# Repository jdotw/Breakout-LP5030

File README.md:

# MP2359, LP5030 and TCA9544A Breakout Board

This breakout board allows you to test an LP5030 LED driver, with a TCA9544A i2c mux/hub, being powered by a MP2359 buck power converter. The board was design to be powered by +12V, but should work with anything from +5 to +12. Place a jumper across the 3.3V 2-pin header to enable the use of the onboard power supply. Or, supply 3.3V directly to the pin marked 3.3V to bypass the onboard power supply. 

I built this board because of a larger project where I wanted to use these three components. However, having not used them before in a design and without access to well priced evaluation board, I decided to make my own. TI sells an eval board for the LP5030 but it's $100+ which is ridiculous. There is a well priced board available to eval the MP2359 but it's rather huge. And so, I decided to build my own. 

The gerber and assembly files included herein have been successfully used with JLCPCB and their SMT Assembly surface to order these boards with everything but the LP5030, TCA9544A and headers already assembled. Those, you'll need to take care of yourself. 

If you have any questions you can find me on Twitter @scotchandcode, and streaming regularly at twitch.tv/jdotw. 

Datasheet links:

MP2359: https://www.monolithicpower.com/en/mp2359.html

LP5030: https://www.ti.com/product/LP5030

TCA9544A: https://www.ti.com/product/TCA9544A

Enjoy! 

-jw

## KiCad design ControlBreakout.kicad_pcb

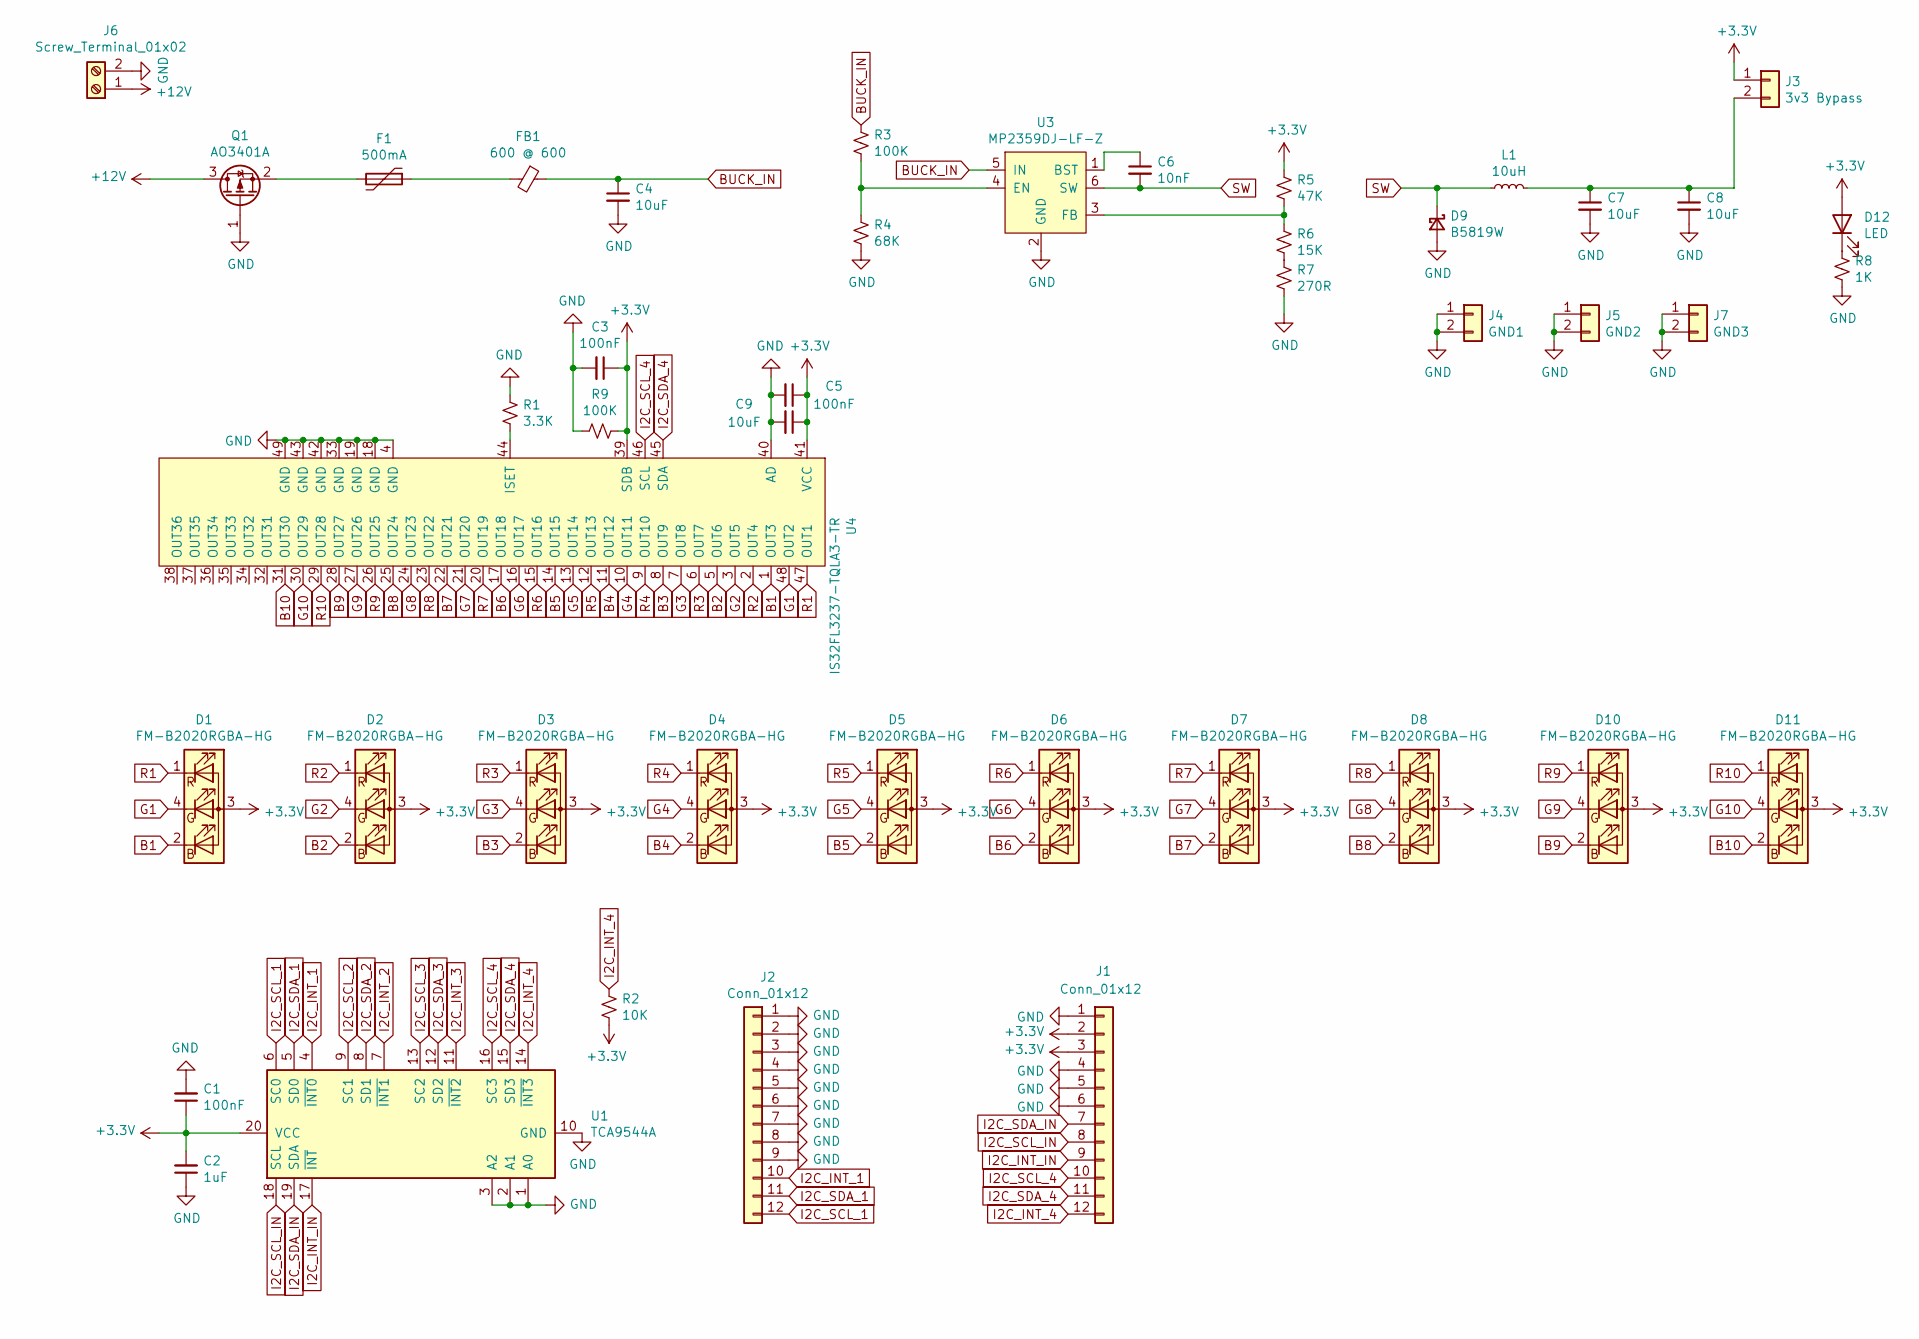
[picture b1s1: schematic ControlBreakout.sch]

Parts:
C1: 100nF; C_0402_1005Metric; LCSC C1525
C2: 1uF; C_0402_1005Metric; LCSC C52923
C3, C5: 100nF; C_0603_1608Metric; LCSC C14663
C4: 10uF; C_1206_3216Metric; LCSC C13585
C6: 10nF; C_0805_2012Metric; LCSC C1710
C7, C8: 10uF; C_1206_3216Metric; LCSC C19702
C9: 10uF; C_0603_1608Metric; LCSC C19702
D1, D2, D4, D5, D6, D7, D8, D10, D11: FM-B2020RGBA-HG; LCSC C108793
D3: FM-B2020RGBA-HG
D9: B5819W; D_SOD-123; LCSC C8598
D12: LED; LED_0603_1608Metric; LCSC C72041
F1: 500mA; Fuse_1206_3216Metric; LCSC C369159
FB1: 600 @ 600; L_0805_2012Metric; LCSC C1017
J1, J2: Conn_01x12; PinHeader_1x12_P2.54mm_Vertical
J3: 3v3 Bypass; PinHeader_1x02_P2.54mm_Vertical
J4: GND1; PinHeader_1x02_P2.54mm_Vertical
J5: GND2; PinHeader_1x02_P2.54mm_Vertical
J6: Screw_Terminal_01x02; TerminalBlock_bornier-2_P5.08mm
J7: GND3; PinHeader_1x02_P2.54mm_Vertical
L1: 10uH; L_Sunlord_MWSA0518_5.4x5.2mm; LCSC C139506
Q1: AO3401A; SOT-23; LCSC C15127
R1: 3.3K; R_0603_1608Metric; LCSC C22978
R2: 10K; R_0603_1608Metric; LCSC C25804
R3: 100K; R_1206_3216Metric; LCSC C17900
R4: 68K; R_0603_1608Metric; LCSC C23231
R5: 47K; R_0603_1608Metric; LCSC C25819
R6: 15K; R_0603_1608Metric; LCSC C22809
R7: 270R; R_0603_1608Metric; LCSC C22966
R8: 1K; R_0603_1608Metric; LCSC C21190
R9: 100K; R_0603_1608Metric; LCSC C25803
U1: TCA9544A; TSSOP-20_4.4x6.5mm_P0.65mm
U3: MP2359DJ-LF-Z; TSOT-23-6; LCSC C14259
U4: IS32FL3237-TQLA3-TR; TQFP-48-1EP_7x7mm_P0.5mm_EP5x5mm

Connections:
+3V3: C1.1, C2.2, C3.1, C5.1, C9.1, D1.3 (+), D2.3 (+), D3.3 (+), D4.3 (+), D5.3 (+), D6.3 (+), D7.3 (+), D8.3 (+), D10.3 (+), D11.3 (+), D12.2 (A), J1.2, J1.3, J3.1, R2.2, R5.1, R9.2, U1.20 (VCC), U4.39 (SDB), U4.41 (VCC)
+12V: J6.1, Q1.3 (D)
B1: D1.2 (B-), U4.1 (OUT3)
B2: D2.2 (B-), U4.5 (OUT6)
B3: D3.2 (B-), U4.8 (OUT9)
B4: D4.2 (B-), U4.11 (OUT12)
B5: D5.2 (B-), U4.14 (OUT15)
B6: D6.2 (B-), U4.17 (OUT18)
B7: D7.2 (B-), U4.22 (OUT21)
B8: D8.2 (B-), U4.25 (OUT24)
B9: D10.2 (B-), U4.28 (OUT27)
B10: D11.2 (B-), U4.31 (OUT30)
BUCK_IN: C4.1, FB1.1, R3.1, U3.5 (IN)
G1: D1.4 (G-), U4.48 (OUT2)
G2: D2.4 (G-), U4.3 (OUT5)
G3: D3.4 (G-), U4.7 (OUT8)
G4: D4.4 (G-), U4.10 (OUT11)
G5: D5.4 (G-), U4.13 (OUT14)
G6: D6.4 (G-), U4.16 (OUT17)
G7: D7.4 (G-), U4.21 (OUT20)
G8: D8.4 (G-), U4.24 (OUT23)
G9: D10.4 (G-), U4.27 (OUT26)
G10: D11.4 (G-), U4.30 (OUT29)
GND: C1.2, C2.1, C3.2, C4.2, C5.2, C7.2, C8.2, C9.2, D9.2 (A), J1.1, J1.4, J1.5, J1.6, J2.1, J2.2, J2.3, J2.4, J2.5, J2.6, J2.7, J2.8, J2.9, J4.1, J4.2, J5.1, J5.2, J6.2, J7.1, J7.2, Q1.1 (G), R1.1, R4.2, R7.2, R8.2, R9.1, U1.1 (A0), U1.2 (A1), U1.3 (A2), U1.10 (GND), U3.2 (GND), U4.4 (GND), U4.18 (GND), U4.19 (GND), U4.33 (GND), U4.40 (AD), U4.42 (GND), U4.43 (GND), U4.49 (GND)
I2C_INT_1: J2.10, U1.4 (~INT0)
I2C_INT_2: U1.7 (~INT1)
I2C_INT_3: U1.11 (~INT2)
I2C_INT_4: J1.12, R2.1, U1.14 (~INT3)
I2C_INT_IN: J1.9, U1.17 (~INT)
I2C_SCL_1: J2.12, U1.6 (SC0)
I2C_SCL_2: U1.9 (SC1)
I2C_SCL_3: U1.13 (SC2)
I2C_SCL_4: J1.10, U1.16 (SC3), U4.46 (SCL)
I2C_SCL_IN: J1.8, U1.18 (SCL)
I2C_SDA_1: J2.11, U1.5 (SD0)
I2C_SDA_2: U1.8 (SD1)
I2C_SDA_3: U1.12 (SD2)
I2C_SDA_4: J1.11, U1.15 (SD3), U4.45 (SDA)
I2C_SDA_IN: J1.7, U1.19 (SDA)
unnamed: C6.1, U3.1 (BST)
unnamed: C7.1, C8.1, J3.2, L1.2
unnamed: D12.1 (K), R8.1
unnamed: F1.1, FB1.2
unnamed: F1.2, Q1.2 (S)
unnamed: R1.2, U4.44 (ISET)
unnamed: R3.2, R4.1, U3.4 (EN)
unnamed: R5.2, R6.1, U3.3 (FB)
unnamed: R6.2, R7.1
R1: D1.1 (R-), U4.47 (OUT1)
R2: D2.1 (R-), U4.2 (OUT4)
R3: D3.1 (R-), U4.6 (OUT7)
R4: D4.1 (R-), U4.9 (OUT10)
R5: D5.1 (R-), U4.12 (OUT13)
R6: D6.1 (R-), U4.15 (OUT16)
R7: D7.1 (R-), U4.20 (OUT19)
R8: D8.1 (R-), U4.23 (OUT22)
R9: D10.1 (R-), U4.26 (OUT25)
R10: D11.1 (R-), U4.29 (OUT28)
SW: C6.2, D9.1 (K), L1.1, U3.6 (SW)

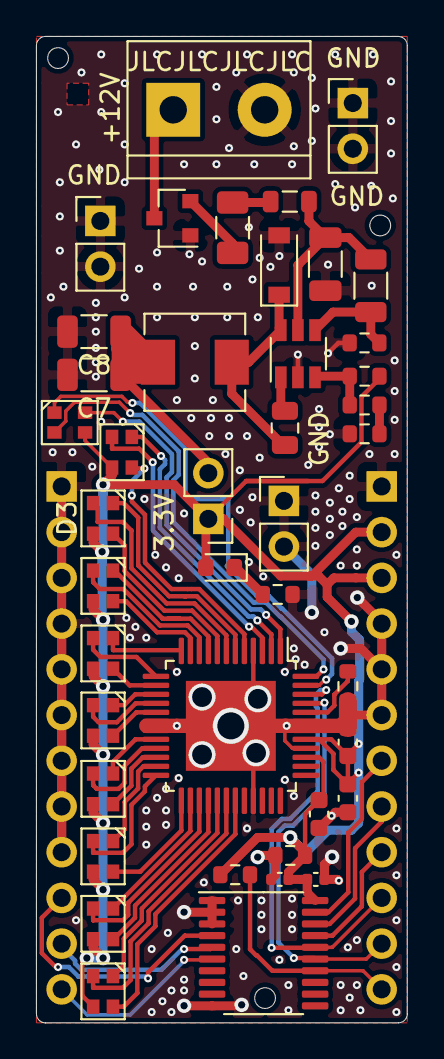
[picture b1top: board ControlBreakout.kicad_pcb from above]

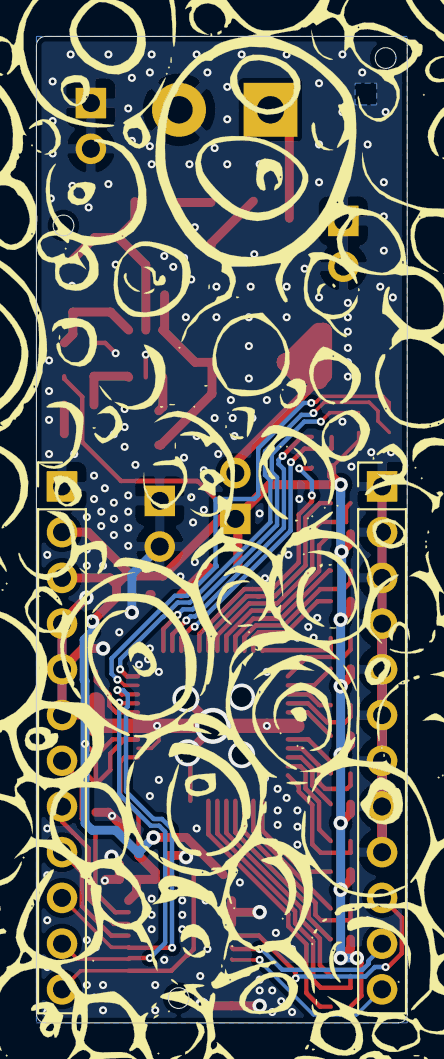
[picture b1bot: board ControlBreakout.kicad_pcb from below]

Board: 2 copper layers, 20.6 x 54.8 mm, 44 parts (2 on the bottom side), 53 nets.

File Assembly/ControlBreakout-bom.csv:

Comment,Designator,Footprint,LCSC
"100nF","C1","Capacitor_SMD:C_0402_1005Metric","C1525"
"10uF","C4","Capacitor_SMD:C_1206_3216Metric","C13585"
"1uF","C2,C3,C5","Capacitor_SMD:C_0402_1005Metric","C52923"
"10nF","C6","Capacitor_SMD:C_0805_2012Metric","C1710"
"10uF","C7,C8","Capacitor_SMD:C_0603_1608Metric","C19702"
"FM-B2020RGBA-HG","D1,D2,D3,D4,D5,D6,D7,D8,D10,D11","fm-b2020rgba-hg:FM-B2020RGBA-HG","C108793"
"LED","D12","LED_SMD:LED_0603_1608Metric","C72041"
"B5819W","D9","Diode_SMD:D_SOD-123","C8598"
"500mA","F1","Fuse:Fuse_1206_3216Metric","C369159"
"600 @ 600","FB1","Inductor_SMD:L_0805_2012Metric","C1017"
"Conn_01x12","J1,J2","Connector_PinHeader_2.54mm:PinHeader_1x12_P2.54mm_Vertical",""
"3v3 Bypass","J3","Connector_PinHeader_2.54mm:PinHeader_1x02_P2.54mm_Vertical",""
"GND1","J4","Connector_PinHeader_2.54mm:PinHeader_1x02_P2.54mm_Vertical",""
"GND2","J5","Connector_PinHeader_2.54mm:PinHeader_1x02_P2.54mm_Vertical",""
"Screw_Terminal_01x02","J6","TerminalBlock:TerminalBlock_bornier-2_P5.08mm",""
"GND3","J7","Connector_PinHeader_2.54mm:PinHeader_1x02_P2.54mm_Vertical",""
"10uH","L1","Inductor_SMD:L_Sunlord_MWSA0518_5.4x5.2mm","C139506"
"AO3401A","Q1","Package_TO_SOT_SMD:SOT-23","C15127"
"3K","R1","Resistor_SMD:R_0603_1608Metric","C4211"
"10K","R2","Resistor_SMD:R_0603_1608Metric","C25804"
"100K","R3","Resistor_SMD:R_1206_3216Metric","C17900"
"68K","R4","Resistor_SMD:R_0603_1608Metric","C23231"
"47K","R5","Resistor_SMD:R_0603_1608Metric","C25819"
"15K","R6","Resistor_SMD:R_0603_1608Metric","C22809"
"270R","R7","Resistor_SMD:R_0603_1608Metric","C22966"
"1K","R8","Resistor_SMD:R_0603_1608Metric","C21190"
"TCA9544A","U1","Package_SO:TSSOP-20_4.4x6.5mm_P0.65mm",""
"LP5030","U2","Package_DFN_QFN:VQFN-46-1EP_5x6mm_P0.4mm_EP2.8x3.8mm",""
"MP2359DJ-LF-Z","U3","Package_TO_SOT_SMD:TSOT-23-6","C14259"

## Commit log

2021-01-09 Breakout board for MP2359 power regulator, LP5030 LED driver, and TCA9544A i2c mux
2021-01-09 Added readme.
2021-01-18 Version 1
2021-01-20 nearly done on v2
2021-01-20 First attempt at ordering
